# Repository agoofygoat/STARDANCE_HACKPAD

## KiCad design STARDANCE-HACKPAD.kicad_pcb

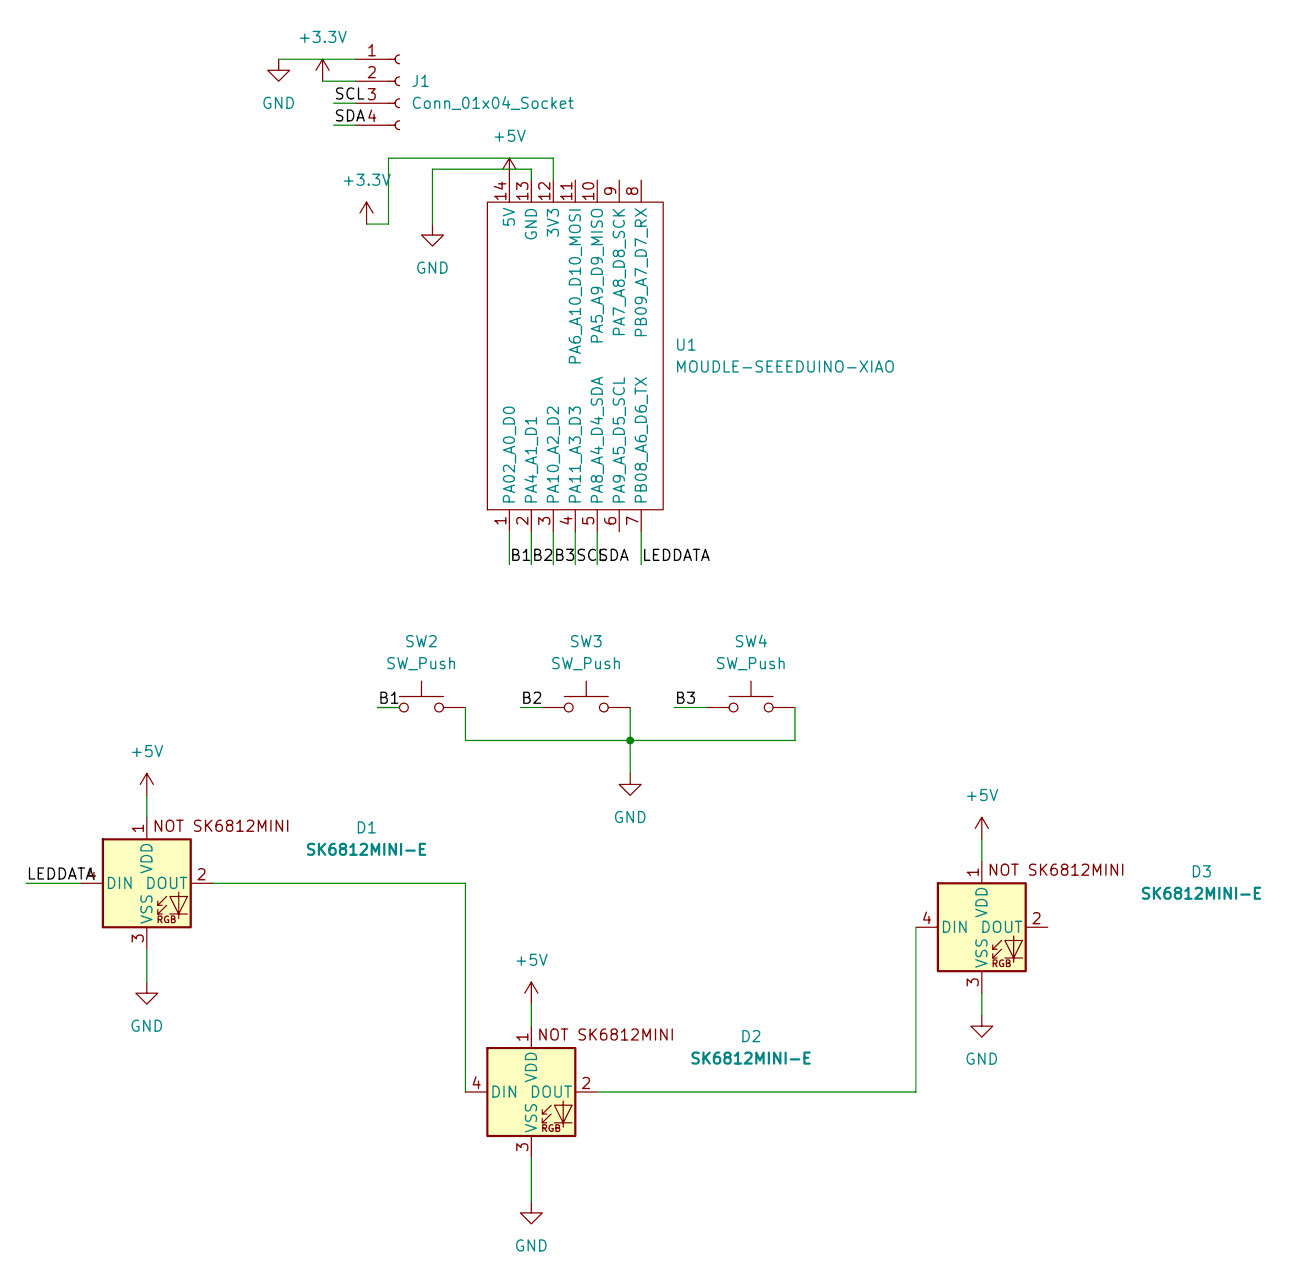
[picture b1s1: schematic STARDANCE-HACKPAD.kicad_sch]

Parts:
D1, D2, D3: SK6812MINI-E; LED_SK6812MINI-E_3.2x2.8mm_P1.5mm_ReverseMount
J1: Conn_01x04_Socket; PinHeader_1x04_P2.54mm_Vertical
SW2, SW3, SW4: SW_Push; SW_Cherry_MX_1.00u_Plate
U1: MOUDLE-SEEEDUINO-XIAO; PinHeader_2x07_P2.54mm_Vertical

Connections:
+3.3V: J1.2, U1.12 (3V3)
+5V: D1.1 (VDD), D2.1 (VDD), D3.1 (VDD), U1.14 (5V)
/B1: SW2.1, U1.1 (PA02_A0_D0)
/B2: SW3.1, U1.2 (PA4_A1_D1)
/B3: SW4.1, U1.3 (PA10_A2_D2)
/LEDDATA: D1.4 (DIN), U1.7 (PB08_A6_D6_TX)
/SCL: J1.3, U1.4 (PA11_A3_D3)
/SDA: J1.4, U1.5 (PA8_A4_D4_SDA)
GND: D1.3 (VSS), D2.3 (VSS), D3.3 (VSS), J1.1, SW2.2, SW3.2, SW4.2, U1.13 (GND)
unnamed: D1.2 (DOUT), D2.4 (DIN)
unnamed: D2.2 (DOUT), D3.4 (DIN)

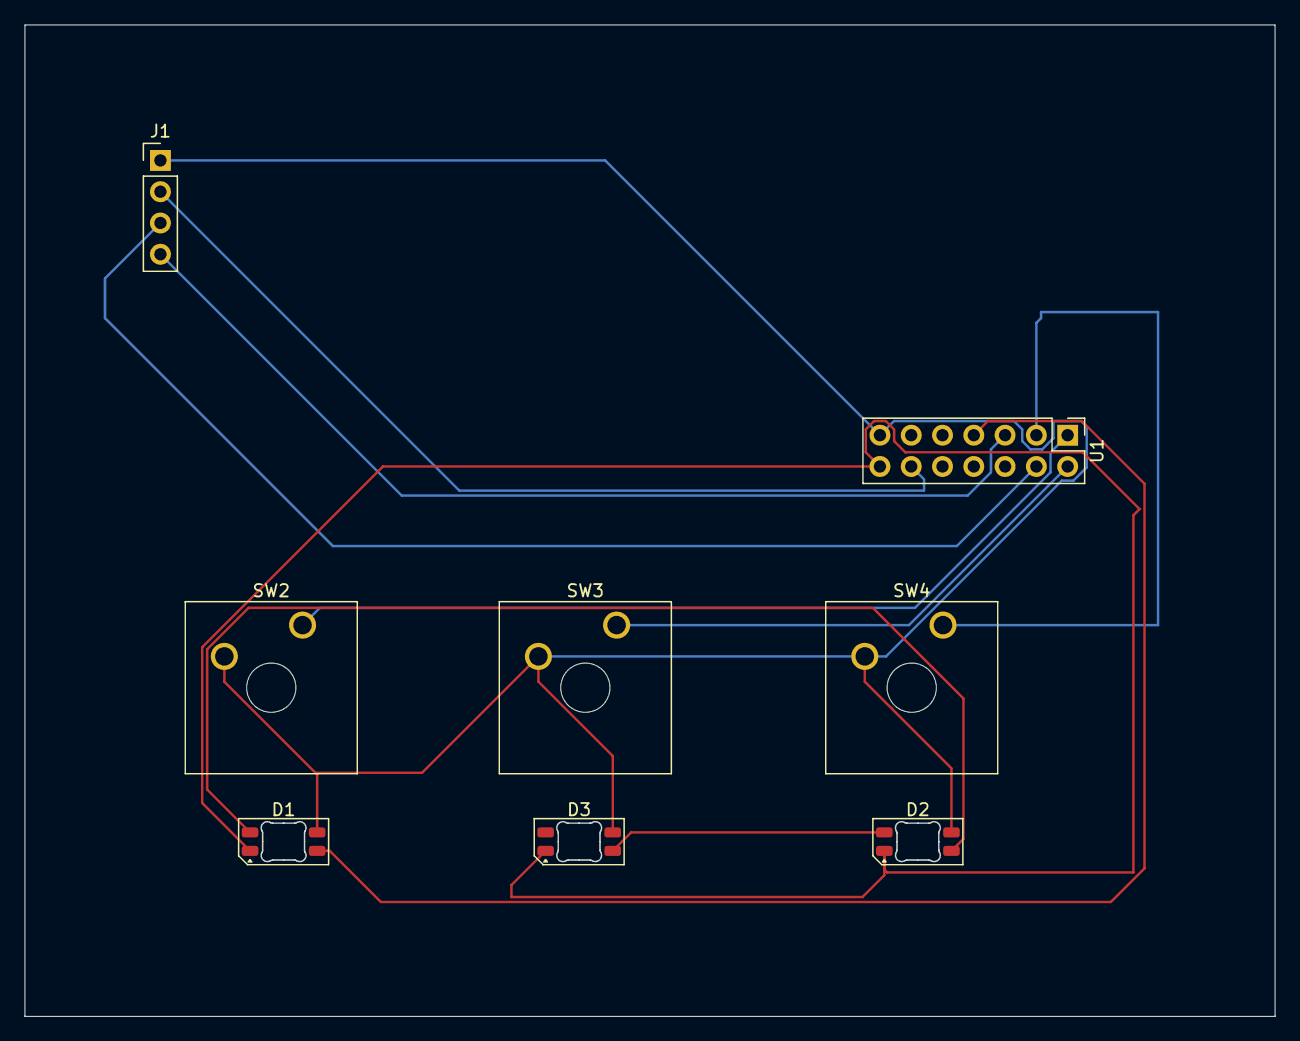
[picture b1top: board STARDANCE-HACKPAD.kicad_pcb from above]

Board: 2 copper layers, 101.5 x 80.5 mm, 8 parts (0 on the bottom side), 11 nets.
